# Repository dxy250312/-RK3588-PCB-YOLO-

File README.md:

# 基于 RK3588 的 PCB 缺陷 YOLO 智能检测系统

English name: PCB Defect YOLO Intelligent Inspection System on RK3588

本项目是一个面向 PCB 裸板缺陷检测的边缘 AI 工程，包含 YOLOv11-P2 模型配置、训练脚本、ONNX 导出、RKNN 转换、RK3588 端推理、GPIO 控制、摄像头预览/拍照和图形界面源码。

This project is an edge AI inspection system for bare PCB defect detection. It provides YOLOv11-P2 model configuration, training scripts, ONNX export, RKNN conversion, RK3588 inference, GPIO control, camera preview/capture, and desktop UI source code.

## 项目简介 / Project Introduction

系统用于在 RK3588 开发板上完成 PCB 缺陷检测闭环：UI 预览摄像头画面，光电传感器触发拍照，RKNN 模型完成缺陷检测，UI 显示结果，GPIO 输出可用于报警。

The system runs a complete PCB inspection loop on RK3588: the UI previews camera frames, the photoelectric sensor triggers capture, RKNN inference detects defects, the UI displays results, and GPIO output can drive an alarm.

当前检测类别 / Current classes:

- `Mouse_bite`
- `Open_circuit`
- `Short`
- `Spur`
- `Spurious_copper`

检测数量和置信度均来自模型推理与标准后处理结果。

Detection counts and confidence values come from model inference and standard post-processing.

## 功能介绍 / Features

- YOLOv11-P2 PCB 小目标缺陷检测模型配置。
- YOLO 格式数据集配置模板。
- 模型训练与单图预测脚本。
- PyTorch 权重到 ONNX 的导出脚本。
- ONNX 到 RKNN 的转换脚本。
- RK3588 端 RKNNLite 推理脚本。
- 标准置信度过滤、NMS、结果图绘制和四行结果文本输出。
- GPIO 输入/输出控制示例。
- GTK4 + Vala 图形界面源码。
- Qt/C++ 参考界面源码。

English:

- YOLOv11-P2 model configuration for small PCB defects.
- YOLO-format dataset template.
- Training and single-image prediction scripts.
- PyTorch-to-ONNX export script.
- ONNX-to-RKNN conversion script.
- RKNNLite inference script for RK3588.
- Standard confidence filtering, NMS, result drawing, and four-line result text output.
- GPIO input/output helper.
- GTK4 + Vala desktop UI source.
- Qt/C++ reference UI source.
- Datasets, images, model binaries, and logs are excluded by `.gitignore`.

## 系统架构 / Architecture

```mermaid
flowchart LR
    A[Camera Preview] --> B[PCB Arrival Sensor]
    B --> C[Image Capture]
    C --> D[Image Enhancement]
    D --> E[RKNN Inference on RK3588]
    E --> F[Post-processing]
    F --> G[result.jpg and result.txt]
    G --> H[GTK or Qt UI]
    F --> I[GPIO Alarm Output]
    H --> J[History and Manual Continue]
```

软件分层 / Software layers:

```mermaid
flowchart TB
    UI[GTK or Qt UI] --> FLOW[Inspection Flow Control]
    FLOW --> CAM[Camera Capture]
    FLOW --> GPIO[GPIO Sensor and Alarm]
    FLOW --> DET[RKNN Detection]
    DET --> POST[YOLO Post-processing]
    POST --> OUT[Result Files]
    OUT --> UI
```

## 项目目录 / Project Structure

```text
.
|-- configs/
|   |-- pcb_dataset.yaml
|   |-- deployment/
|   |   |-- photo.txt
|   |   `-- rknn_runtime.yaml
|   `-- models/
|       `-- yolo11n-p2-pcb.yaml
|-- docs/
|   |-- DATASET.md
|   |-- MODEL.md
|   |-- RKNN_DEPLOYMENT.md
|   `-- media/
|       `-- pcb-inspection-demo.mp4
|-- examples/
|   `-- README.md
|-- hardware/
|   `-- extension-board/
|       |-- README.md
|       |-- extension.csv
|       |-- extension.kicad_pcb
|       |-- extension.kicad_pro
|       `-- extension.kicad_sch
|-- models/
|   `-- README.md
|-- src/
|   |-- export/
|   |-- gpio/
|   |-- rknn/
|   `-- training/
|-- ui/
|   |-- gtk/
|   `-- qt/
|-- CHANGELOG.md
|-- CODE_OF_CONDUCT.md
|-- CONTRIBUTING.md
|-- example_dataset.yaml
|-- LICENSE
|-- README.md
|-- requirements.txt
`-- .gitignore
```

## 环境要求 / Requirements

Python:

- Python 3.10+
- PyTorch
- Ultralytics YOLO
- OpenCV
- NumPy
- PyYAML

RKNN:

- RKNN Toolkit 2 for model conversion.
- RKNNLite runtime for RK3588 deployment.

UI:

- GTK4, Vala, Meson, Ninja for `ui/gtk`.
- Qt 6 and CMake for `ui/qt`.

## 安装方法 / Installation

```bash
git clone <repository_url>
cd pcb-defect-yolo-rk3588
python -m venv .venv
source .venv/bin/activate
pip install -r requirements.txt
```

RKNN Toolkit 2 和 RKNNLite runtime 请根据 Rockchip 官方 SDK 或开发板厂商文档安装。

Install RKNN Toolkit 2 and RKNNLite runtime according to the Rockchip SDK or your board vendor documentation.

## 数据集准备 / Dataset

本仓库不提供数据集。请将数据集放在仓库外部，并使用 YOLO 检测格式。

This repository does not provide datasets. Place datasets outside the repository in YOLO detection format.

推荐结构 / Recommended layout:

```text
<dataset_root>/
  images/
    train/
    val/
    test/
  labels/
    train/
    val/
    test/
```

示例配置 / Example configuration:

```text
example_dataset.yaml
configs/pcb_dataset.yaml
```

更多说明见 / See:

```text
docs/DATASET.md
```

## 模型训练 / Training

```bash
python src/training/train_p2.py \
  --model configs/models/yolo11n-p2-pcb.yaml \
  --data configs/pcb_dataset.yaml \
  --weights yolo11n.pt \
  --epochs 100 \
  --imgsz 640 \
  --batch 16
```

单图预测 / Single-image prediction:

```bash
python src/training/predict_image.py \
  --weights <project_root>/weights/best.pt \
  --image <project_root>/samples/pcb.jpg \
  --output <project_root>/results/result_detect.jpg
```

## ONNX 导出 / Export

```bash
python src/export/export_onnx.py \
  --weights <project_root>/weights/best.pt \
  --output <project_root>/export \
  --imgsz 640 \
  --opset 12
```

如果已经有本地 ONNX 文件，可将其放到：

If a local ONNX model already exists, place it at:

```text
<project_root>/export/best.onnx
```

## RKNN 转换 / RKNN Conversion

```bash
python src/export/onnx_to_rknn.py \
  --onnx <project_root>/export/best.onnx \
  --output <project_root>/models/best-rk3588.rknn \
  --target rk3588
```

模型二进制文件只在本地使用，不提交到仓库。

Model binaries are used locally only and are not committed.

## RK3588 部署 / Deployment

在 RK3588 上运行推理：

Run inference on RK3588:

```bash
python src/rknn/pcb_detect.py \
  --model <project_root>/models/best-rk3588.rknn \
  --image <project_root>/samples/pcb.jpg \
  --time_file <project_root>/runtime/capture_time.txt \
  --output_dir <project_root>/runtime/output \
  --conf 0.25
```

输出 / Outputs:

```text
runtime/output/result.jpg
runtime/output/result.txt
```

`result.txt` 格式 / format:

```text
YES or NO
defect_count
defect_type confidence, ...
detection_time
```

## GPIO 控制 / GPIO

GPIO 示例脚本：

GPIO helper:

```bash
python src/gpio/gpio_control.py --gpio 105 --direction in
python src/gpio/gpio_control.py --gpio 103 --direction out --value 1 --hold-ms 3000
```

运行前请根据实际开发板接线修改：

Adjust the following file for your board wiring:

```text
configs/deployment/rknn_runtime.yaml
```

## UI 界面 / GTK and Qt UI

### GTK4 + Vala

GTK UI 位于 `ui/gtk`，是开发板端桌面 UI 主工程。

The GTK UI is in `ui/gtk` and is the main desktop UI project for the board.

```bash
sudo apt install valac meson ninja-build libgtk-4-dev libjson-glib-dev libgdk-pixbuf-2.0-dev
cd ui/gtk
meson setup build
ninja -C build
./build/pcb-inspector-gtk
```

摄像头预览命令模板 / Camera preview template:

```text
configs/deployment/photo.txt
```

### Qt/C++

Qt 参考界面位于 `ui/qt`。

The Qt reference UI is in `ui/qt`.

```bash
cd ui/qt
cmake -S . -B build
cmake --build build
```

## 运行效果 / Results

演示视频 / Demo video:

```text
docs/media/pcb-inspection-demo.mp4
```

运行后系统会生成：

Runtime outputs:

```text
runtime/output/result.jpg
runtime/output/result.txt
```

由于本仓库不上传企业图片、采集图片或检测结果图片，README 不展示真实检测图片。用户可以在本地运行后查看 `runtime/output/result.jpg`。

This repository does not upload business images, captured images, or result images. After local deployment, users can view `runtime/output/result.jpg`.

## TODO

- Add public demo images that are safe to redistribute.
- Add automated unit tests for post-processing.
- Add CI checks for Python syntax and repository hygiene.
- Add a detailed wiring diagram for a reference RK3588 board.
- Add packaging scripts for board-side deployment.

## License

本项目采用 MIT License，详见 `LICENSE`。

This project is released under the MIT License. See `LICENSE`.

Ultralytics YOLO and Rockchip RKNN packages are third-party dependencies and follow their own licenses. This repository does not vendor the Ultralytics source tree and does not distribute model binaries.

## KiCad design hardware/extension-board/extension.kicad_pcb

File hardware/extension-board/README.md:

# Extension Board Hardware

This directory contains the KiCad source files for the RK3588 PCB inspection extension board.

Files:

- `extension.kicad_sch`: schematic source.
- `extension.kicad_pcb`: PCB layout source.
- `extension.kicad_pro`: KiCad project file.
- `extension.csv`: exported component list.

Generated manufacturing outputs, editor history, local KiCad session files, and archived Gerber packages are not committed.

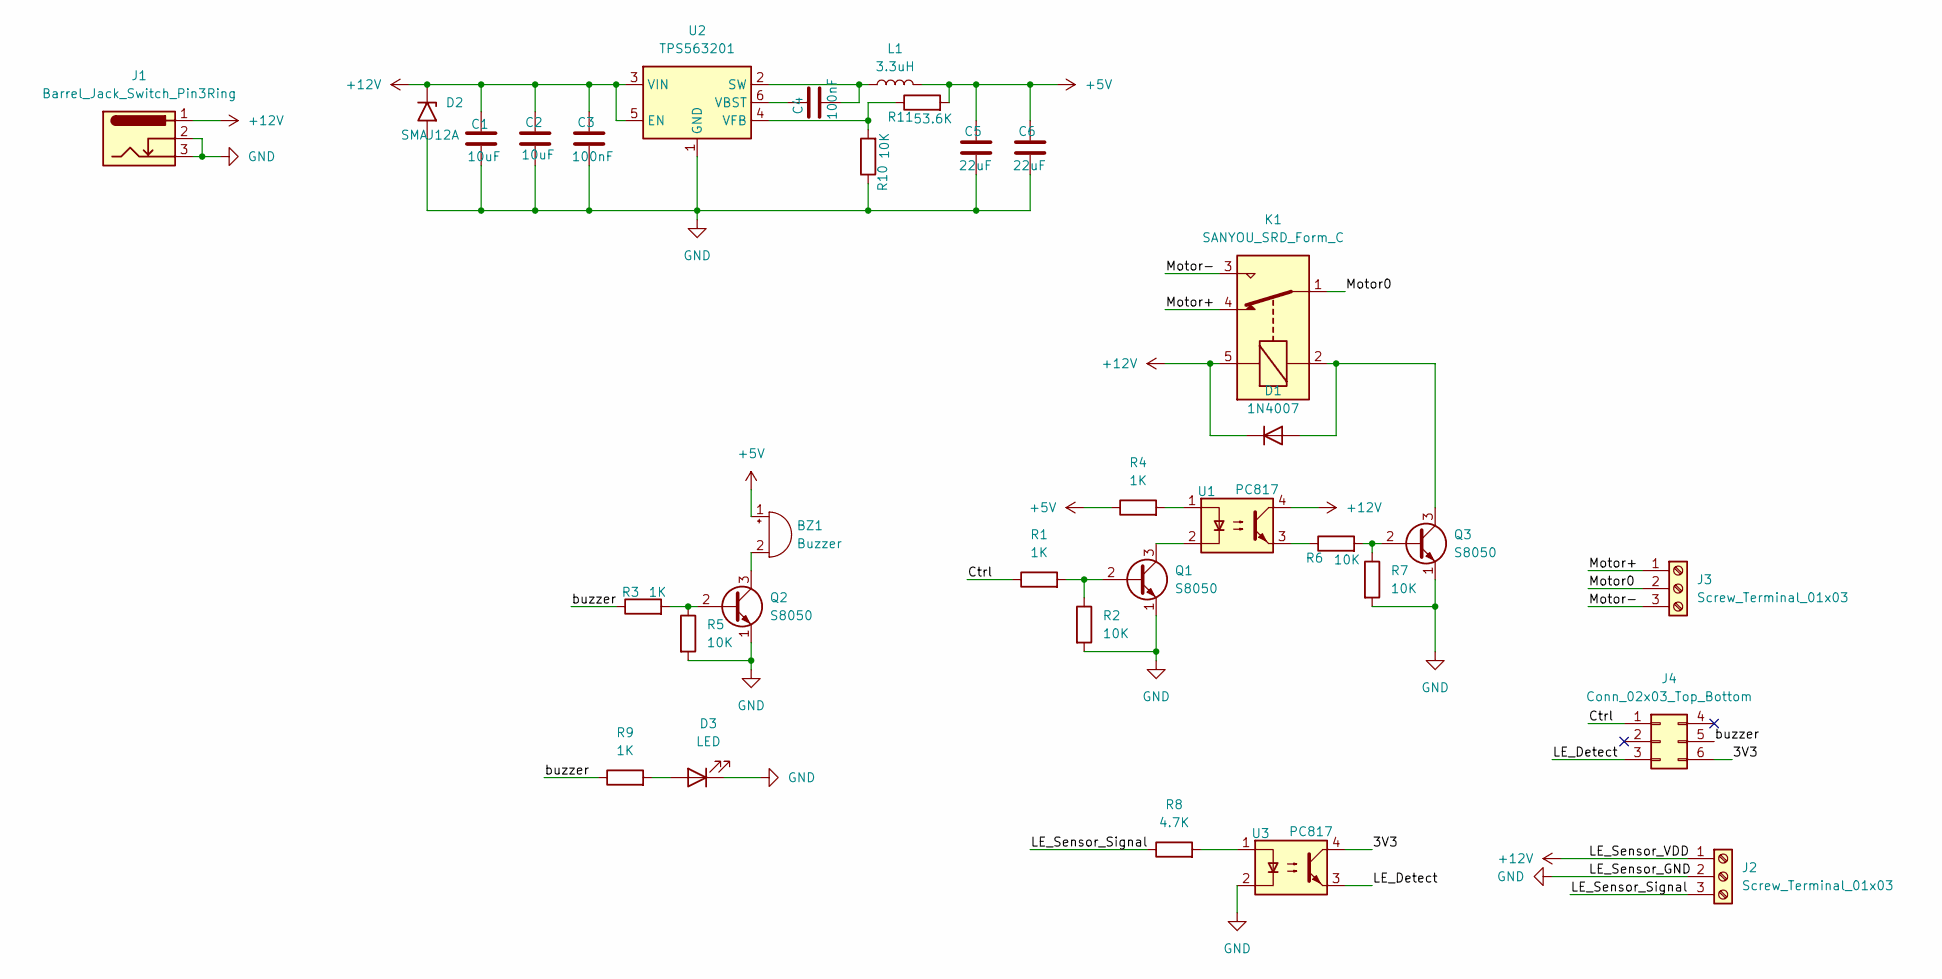
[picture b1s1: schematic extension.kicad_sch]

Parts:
BZ1: Buzzer; Buzzer_TDK_PS1240P02BT_D12.2mm_H6.5mm
C1, C2: 10uF; C_Disc_D5.0mm_W2.5mm_P5.00mm
C3, C4: 100nF; C_Disc_D5.0mm_W2.5mm_P5.00mm
C5, C6: 22uF; C_Disc_D5.0mm_W2.5mm_P5.00mm
D1: 1N4007; D_DO-41_SOD81_P10.16mm_Horizontal
D2: SMAJ12A; D_SMA
D3: LED; LED_D3.0mm
J1: Barrel_Jack_Switch_Pin3Ring; BarrelJack_GCT_DCJ200-10-A_Horizontal
J2, J3: Screw_Terminal_01x03; TerminalBlock_RND_205-00046_1x03_P5.00mm_Horizontal
J4: Conn_02x03_Top_Bottom; PinHeader_2x03_P2.54mm_Vertical
K1: SANYOU_SRD_Form_C; Relay_SPDT_SANYOU_SRD_Series_Form_C
L1: 3.3uH; L_6.3x6.3_H3
Q1, Q2, Q3: S8050; TO-92_Inline
R1, R3, R4, R9: 1K; R_Axial_DIN0207_L6.3mm_D2.5mm_P7.62mm_Horizontal
R2, R5, R6, R7, R10: 10K; R_Axial_DIN0207_L6.3mm_D2.5mm_P7.62mm_Horizontal
R8: 4.7K; R_Axial_DIN0207_L6.3mm_D2.5mm_P7.62mm_Horizontal
R11: 53.6K; R_Axial_DIN0207_L6.3mm_D2.5mm_P7.62mm_Horizontal
U1, U3: PC817; DIP-4_W7.62mm
U2: TPS563201; SOT-23-6

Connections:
+5V: BZ1.1 (+), C5.1, C6.1, L1.2, R4.1, R11.2
+12V: C1.1, C2.1, C3.1, D1.1 (K), D2.1 (A1), J1.1, J2.1, K1.5, U1.4, U2.3 (VIN), U2.5 (EN)
/3V3: J4.6, U3.4
/Ctrl: J4.1, R1.1
/LE_Detect: J4.3, U3.3
/LE_Sensor_Signal: J2.3, R8.1
/Motor0: J3.2, K1.1
/Motor+: J3.1, K1.4
/Motor-: J3.3, K1.3
/buzzer: J4.5, R3.1, R9.1
GND: C1.2, C2.2, C3.2, C5.2, C6.2, D2.2 (A2), D3.1 (K), J1.2, J1.3, J2.2, Q1.1 (E), Q2.1 (E), Q3.1 (E), R2.2, R5.2, R7.2, R10.1, U2.1 (GND), U3.2
unnamed: BZ1.2 (-), Q2.3 (C)
unnamed: D1.2 (A), K1.2, Q3.3 (C)
unnamed: D3.2 (A), R9.2
unnamed: Q1.2 (B), R1.2, R2.1
unnamed: Q1.3 (C), U1.2
unnamed: Q2.2 (B), R3.2, R5.1
unnamed: Q3.2 (B), R6.2, R7.1
unnamed: R4.2, U1.1
unnamed: R6.1, U1.3
unnamed: R8.2, U3.1
unnamed: C4.2, L1.1, U2.2 (SW)
unnamed: C4.1, U2.6 (VBST)
unnamed: R10.2, R11.1, U2.4 (VFB)

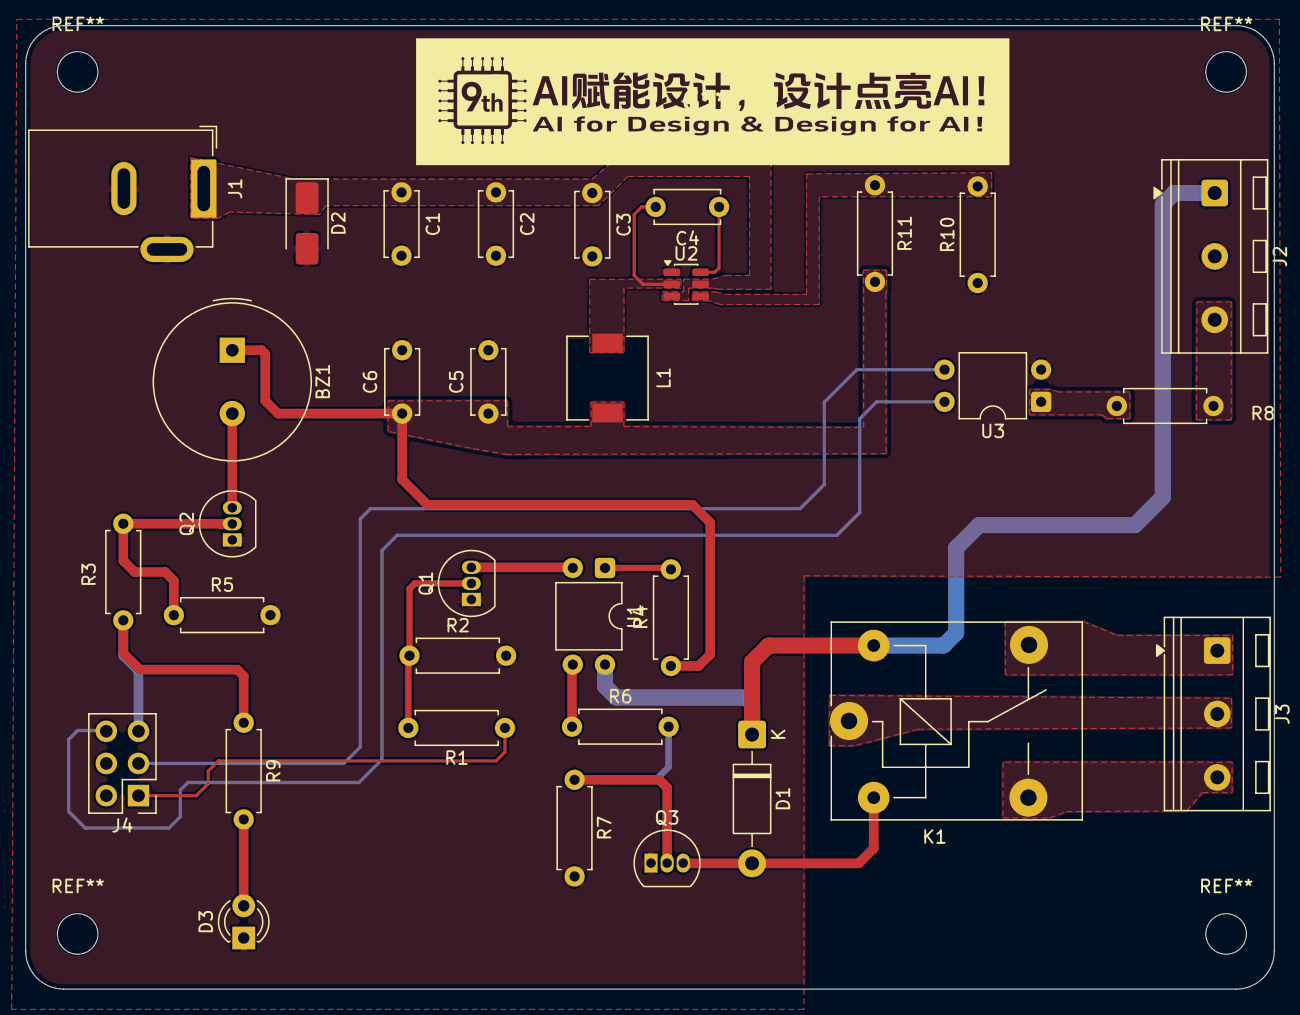
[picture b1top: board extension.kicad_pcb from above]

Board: 2 copper layers, 98.5 x 76.0 mm, 33 parts (0 on the bottom side), 24 nets.
